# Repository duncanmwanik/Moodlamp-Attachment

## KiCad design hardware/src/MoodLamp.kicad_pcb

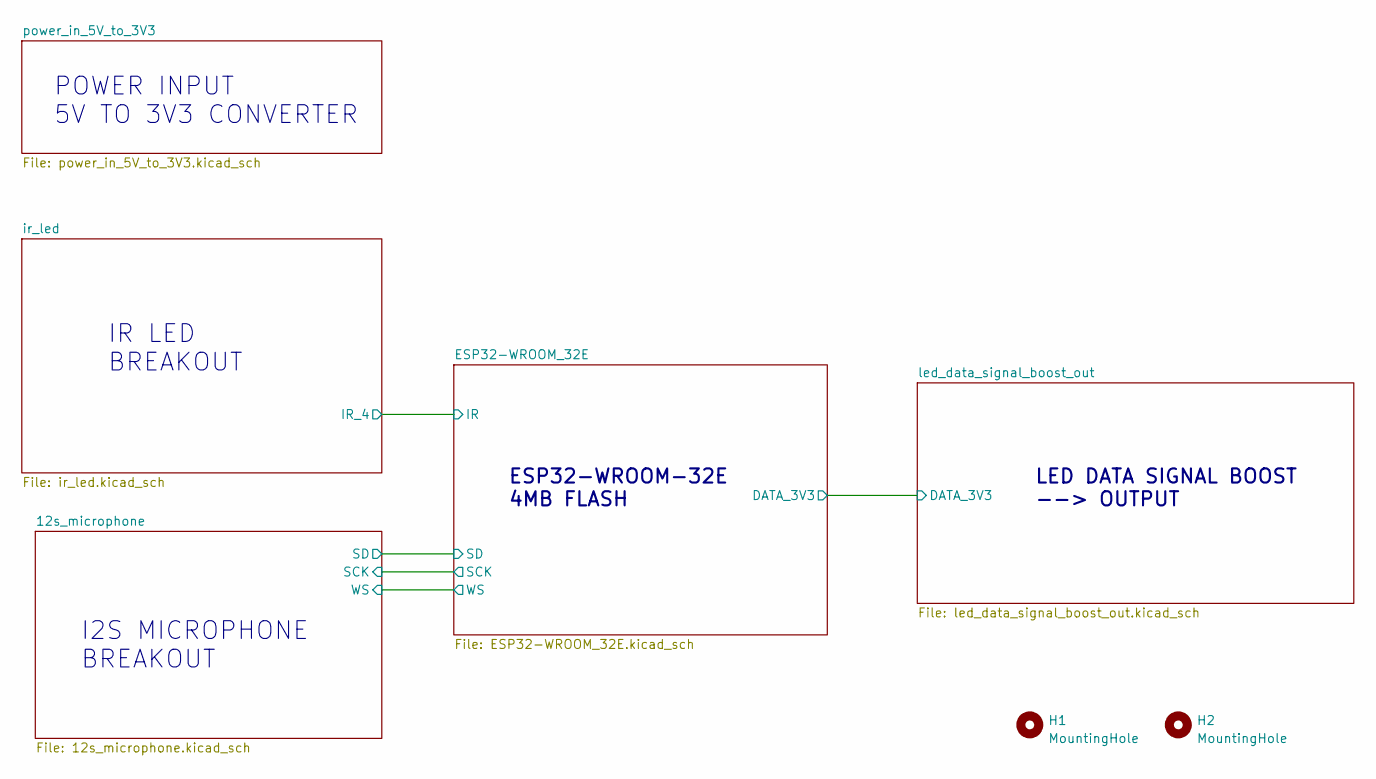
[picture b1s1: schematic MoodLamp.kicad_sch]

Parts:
H1, H2: MountingHole; MountingHole_2.2mm_M2

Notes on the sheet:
ESP32-WROOM-32E 4MB FLASH
I2S MICROPHONE BREAKOUT
LED DATA SIGNAL BOOST --> OUTPUT
IR LED BREAKOUT
POWER INPUT 5V TO 3V3 CONVERTER

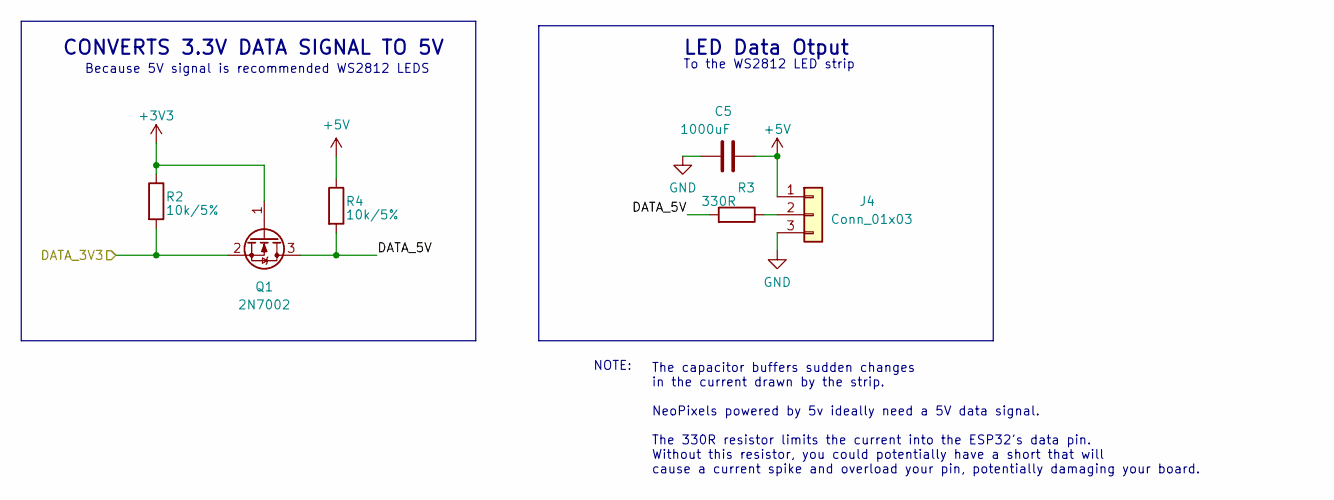
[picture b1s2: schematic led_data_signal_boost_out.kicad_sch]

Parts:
C5: 1000uF; CP_Radial_D8.0mm_P5.00mm
J4: Conn_01x03; PinHeader_1x03_P2.54mm_Vertical
Q1: 2N7002; SOT-23; MPN 2N7002
R2, R4: 10k/5%; R_0603_1608Metric; MPN 0603WAF1002T5E
R3: 330R; R_0603_1608Metric; MPN 0603WAF3300T5E

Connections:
+3V3: Q1.1 (G), R2.1; also elsewhere on the board
+5V: C5.1, J4.1, R4.1; also elsewhere on the board
/ESP32-WROOM_32E/DATA_3V3: Q1.2 (S), R2.2; also elsewhere on the board
/led_data_signal_boost_out/DATA_5V: Q1.3 (D), R3.2, R4.2
GND: C5.2, J4.3; also elsewhere on the board
unnamed: J4.2, R3.1

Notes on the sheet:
CONVERTS 3.3V DATA SIGNAL TO 5V
NOTE:
Because 5V signal is recommended WS2812 LEDS
The capacitor buffers sudden changes in the current drawn by the strip. NeoPixels powered by 5v ideally need a 5V data signal. The 330R resistor limits the current into the ESP32's data pin. Without this resistor, you could potentially have a short that will cause a current spike and overload your 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
LED Data Otput
To the WS2812 LED strip

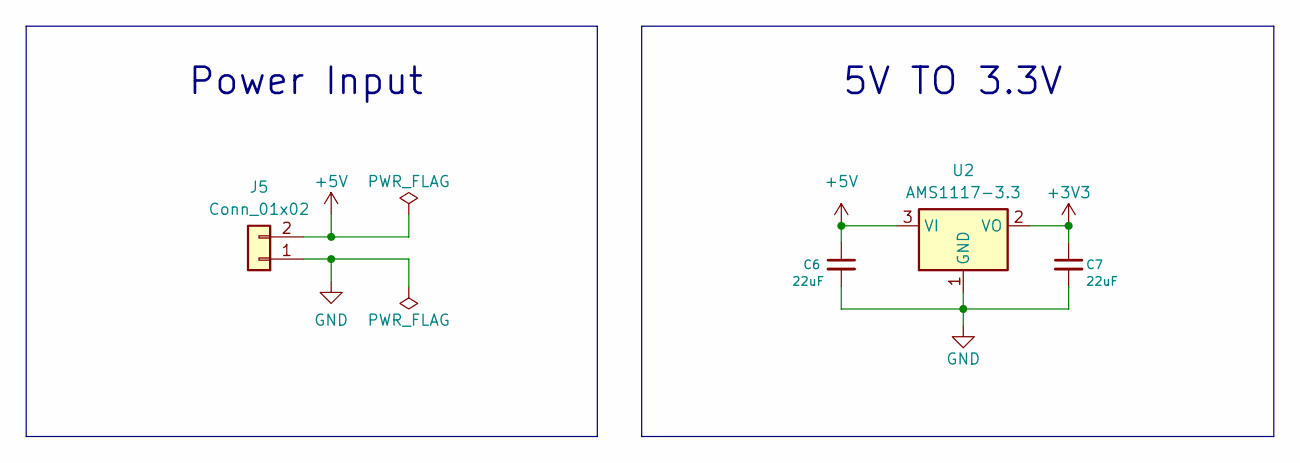
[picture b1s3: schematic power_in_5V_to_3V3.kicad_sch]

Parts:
C6, C7: 22uF; C_1206_3216Metric; MPN CL31A226KPHNNNE
J5: Conn_01x02; PinHeader_1x02_P2.54mm_Vertical
U2: AMS1117-3.3; SOT-223-3_TabPin2; MPN AMS1117-3.3

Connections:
+3V3: C7.1, U2.2 (VO); also elsewhere on the board
+5V: C6.1, J5.2, U2.3 (VI); also elsewhere on the board
GND: C6.2, C7.2, J5.1, U2.1 (GND); also elsewhere on the board

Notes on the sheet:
Power Input
5V TO 3.3V

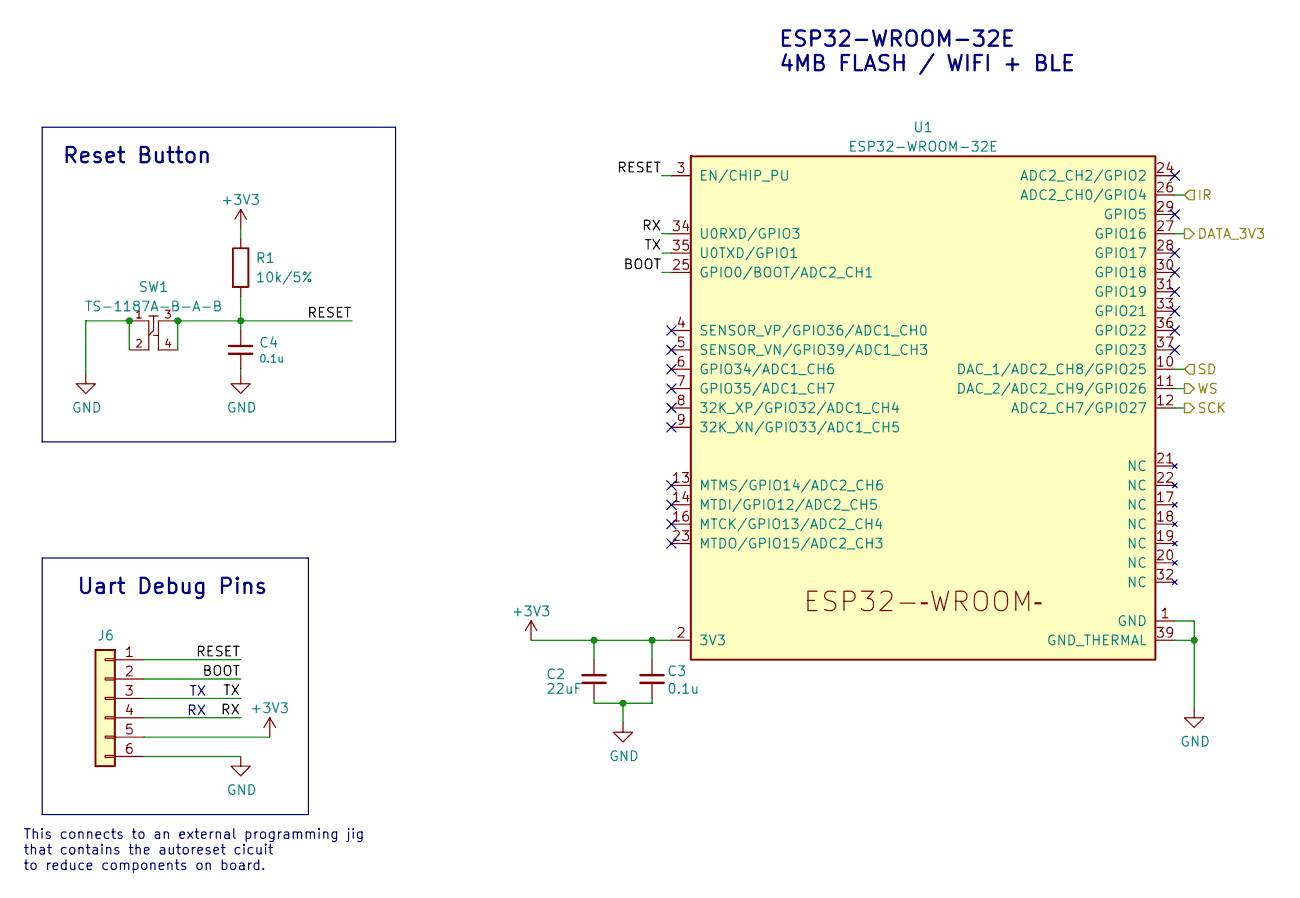
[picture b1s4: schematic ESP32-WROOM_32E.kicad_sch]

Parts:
C2: 22uF; C_1206_3216Metric; MPN CL31A226KPHNNNE
C3, C4: 0.1u; C_0603_1608Metric; MPN CC0603KRX7R9BB104
J6: Conn_01x06; PinHeader_1x06_P2.54mm_Vertical
R1: 10k/5%; R_0603_1608Metric; MPN 0603WAF1002T5E
SW1: TS-1187A-B-A-B; MPN TS-1187A-B-A-B
U1: ESP32-WROOM-32E; MPN ESP32-WROOM-32E-N4

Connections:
+3V3: C2.1, C3.1, J6.5, R1.1, U1.2 (3V3); also elsewhere on the board
/12s_microphone/SCK: U1.12 (ADC2_CH7/GPIO27); also elsewhere on the board
/12s_microphone/SD: U1.10 (DAC_1/ADC2_CH8/GPIO25); also elsewhere on the board
/12s_microphone/WS: U1.11 (DAC_2/ADC2_CH9/GPIO26); also elsewhere on the board
/ESP32-WROOM_32E/BOOT: J6.2, U1.25 (GPIO0/BOOT/ADC2_CH1)
/ESP32-WROOM_32E/DATA_3V3: U1.27 (GPIO16); also elsewhere on the board
/ESP32-WROOM_32E/IR: U1.26 (ADC2_CH0/GPIO4); also elsewhere on the board
/ESP32-WROOM_32E/RESET: C4.1, J6.1, R1.2, SW1.3, SW1.4, U1.3 (EN/CHIP_PU)
/ESP32-WROOM_32E/RX: J6.4, U1.34 (U0RXD/GPIO3)
/ESP32-WROOM_32E/TX: J6.3, U1.35 (U0TXD/GPIO1)
GND: C2.2, C3.2, C4.2, J6.6, SW1.1, SW1.2, U1.1 (GND), U1.15 (GND), U1.38 (GND), U1.39 (GND_THERMAL); also elsewhere on the board

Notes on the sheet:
This connects to an external programming jig that contains the autoreset cicuit to reduce components on board.
Reset Button
Uart Debug Pins
ESP32-WROOM-32E 4MB FLASH / WIFI + BLE

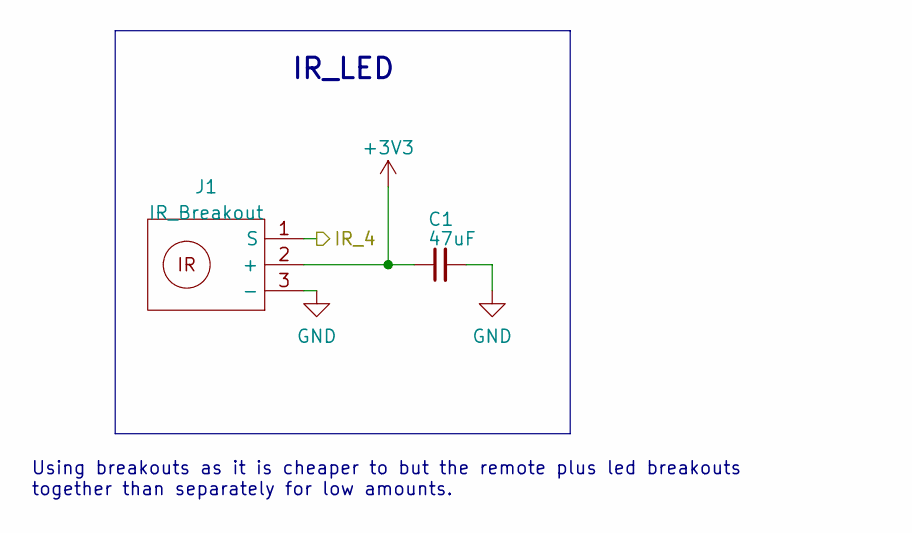
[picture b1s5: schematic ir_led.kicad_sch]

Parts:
C1: 47uF; C_0805_2012Metric; MPN CL21A476MQYNNNE
J1: IR_Breakout

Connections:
+3V3: C1.1, J1.2 (+); also elsewhere on the board
/ESP32-WROOM_32E/IR: J1.1 (S); also elsewhere on the board
GND: C1.2, J1.3 (-); also elsewhere on the board

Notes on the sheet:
IR_LED
Using breakouts as it is cheaper to but the remote plus led breakouts together than separately for low amounts.

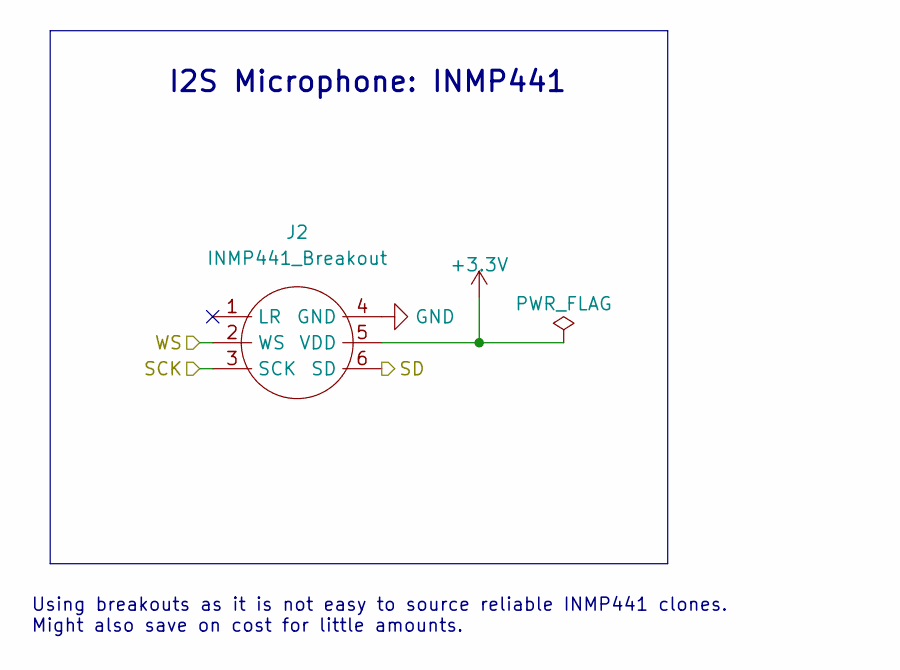
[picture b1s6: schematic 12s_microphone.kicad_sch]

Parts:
J2: INMP441_Breakout

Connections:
+3.3V: J2.5 (VDD)
/12s_microphone/SCK: J2.3 (SCK); also elsewhere on the board
/12s_microphone/SD: J2.6 (SD); also elsewhere on the board
/12s_microphone/WS: J2.2 (WS); also elsewhere on the board
GND: J2.4 (GND); also elsewhere on the board

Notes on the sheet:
Using breakouts as it is not easy to source reliable INMP441 clones. Might also save on cost for little amounts.
I2S Microphone: INMP441

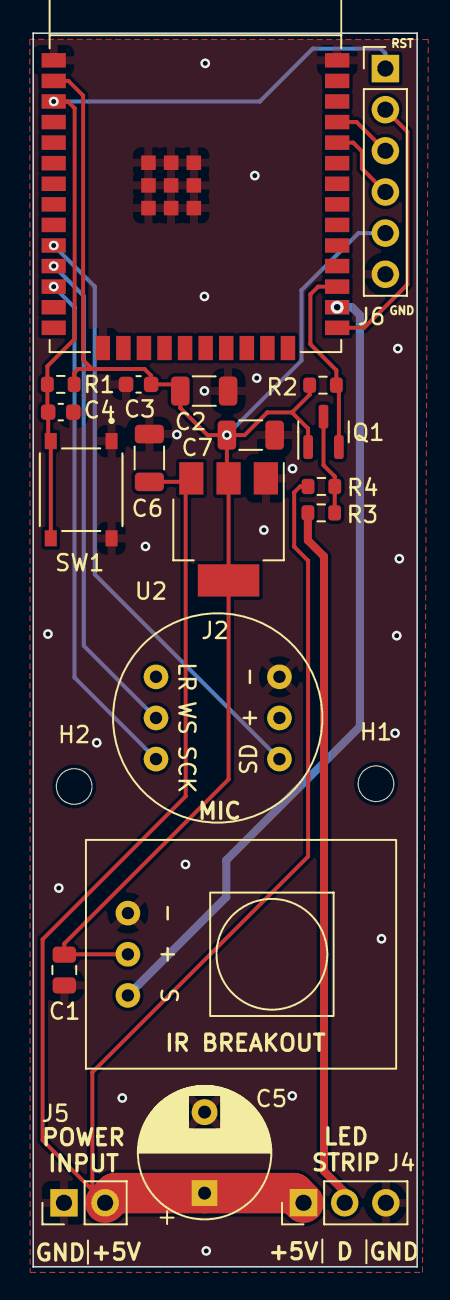
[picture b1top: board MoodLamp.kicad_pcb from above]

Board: 2 copper layers, 23.7 x 76.1 mm, 22 parts (0 on the bottom side), 14 nets.
